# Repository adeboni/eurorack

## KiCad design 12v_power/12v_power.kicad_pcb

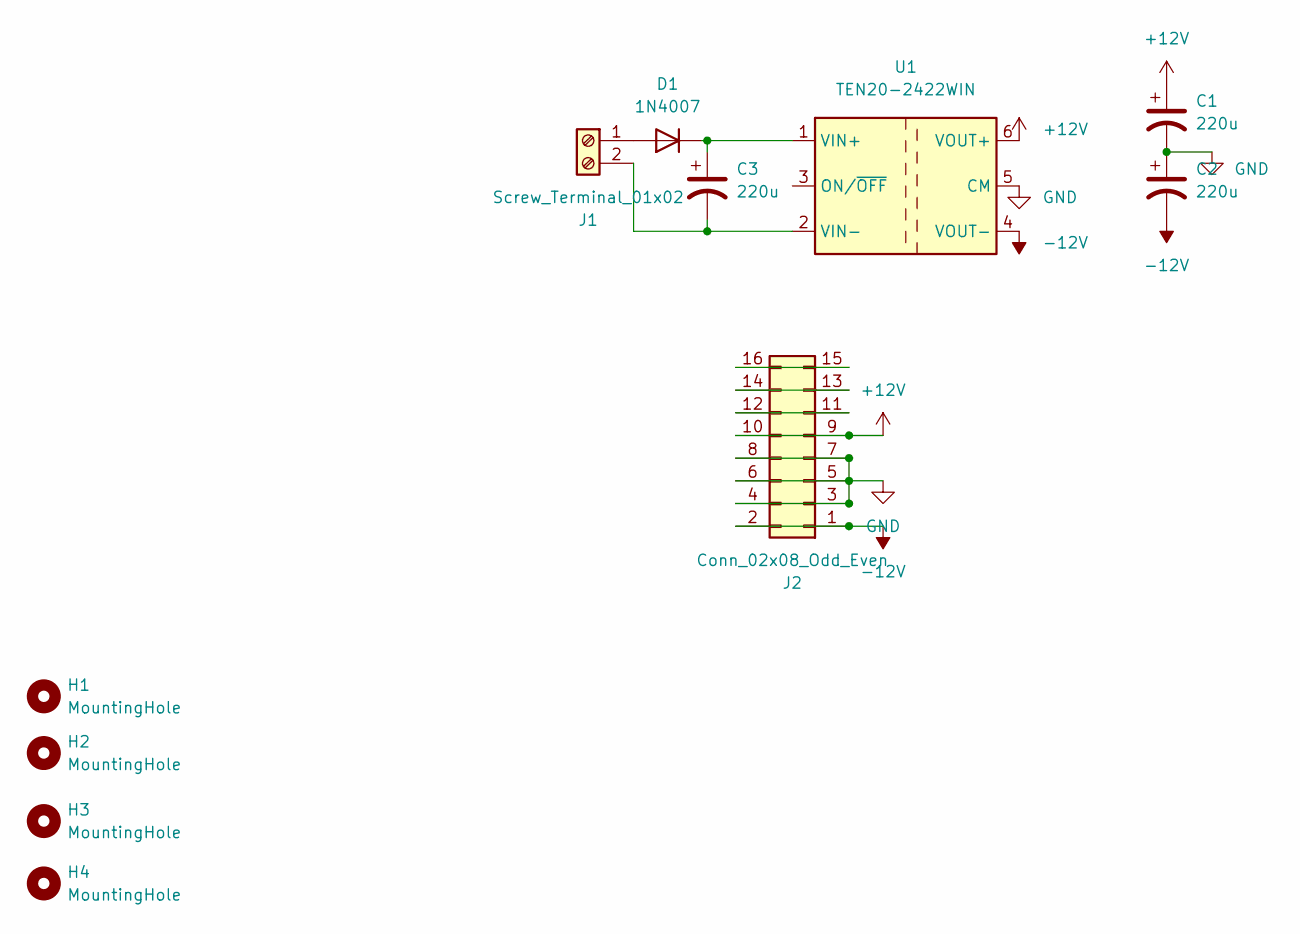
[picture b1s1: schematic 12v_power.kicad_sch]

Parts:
C1, C2, C3: 220u; CP_Radial_D10.0mm_P5.00mm
D1: 1N4007; D_DO-41_SOD81_P10.16mm_Horizontal
H1, H2, H3, H4: MountingHole; MountingHole_3.2mm_M3
J1: Screw_Terminal_01x02; TerminalBlock_Phoenix_MKDS-3-2-5.08_1x02_P5.08mm_Horizontal
J2: Conn_02x08_Odd_Even; IDC-Header_2x08_P2.54mm_Vertical
U1: TEN20-2422WIN; CONV_PYBE30-Q24-D12

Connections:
+12V: C1.1, J2.9, J2.10, U1.6 (VOUT+)
-12V: C2.2, J2.1, J2.2, U1.4 (VOUT-)
GND: C1.2, C2.1, J2.3, J2.4, J2.5, J2.6, J2.7, J2.8, U1.5 (CM)
unnamed: C3.1, D1.1 (K), U1.1 (VIN+)
unnamed: C3.2, J1.2, U1.2 (VIN-)
unnamed: D1.2 (A), J1.1
unnamed: J2.11, J2.12
unnamed: J2.13, J2.14
unnamed: J2.15, J2.16

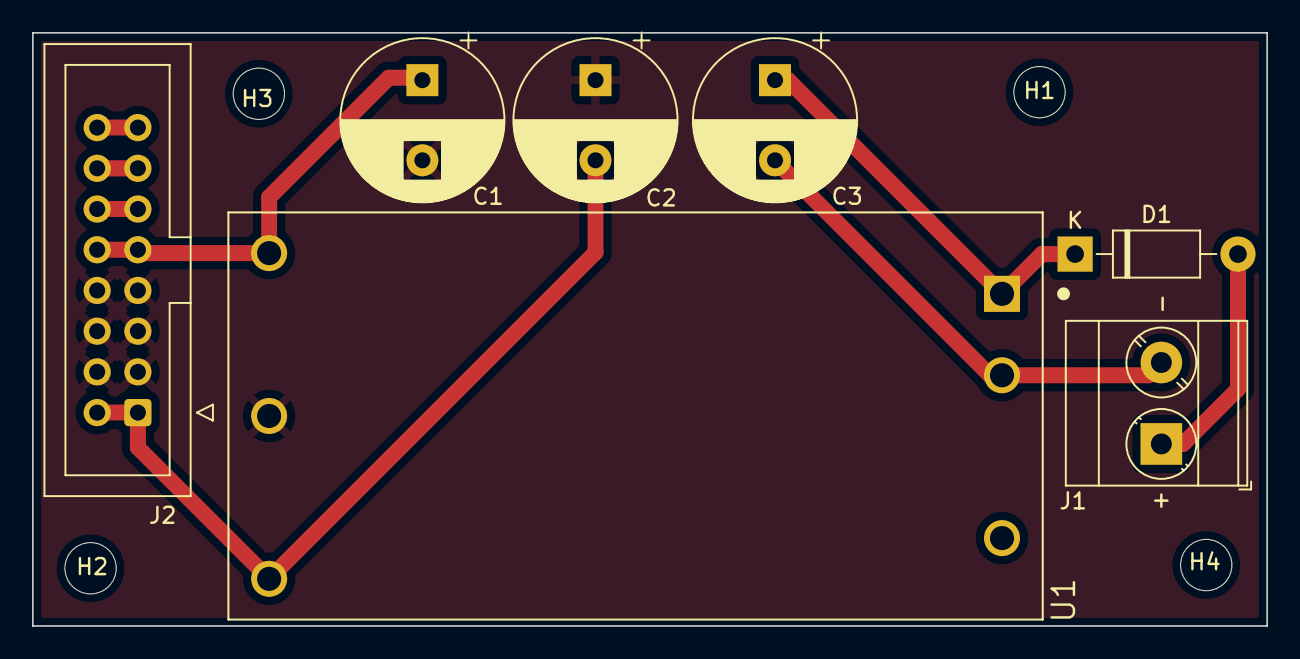
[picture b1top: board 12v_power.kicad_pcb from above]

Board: 2 copper layers, 77.0 x 37.0 mm, 11 parts (0 on the bottom side), 9 nets.

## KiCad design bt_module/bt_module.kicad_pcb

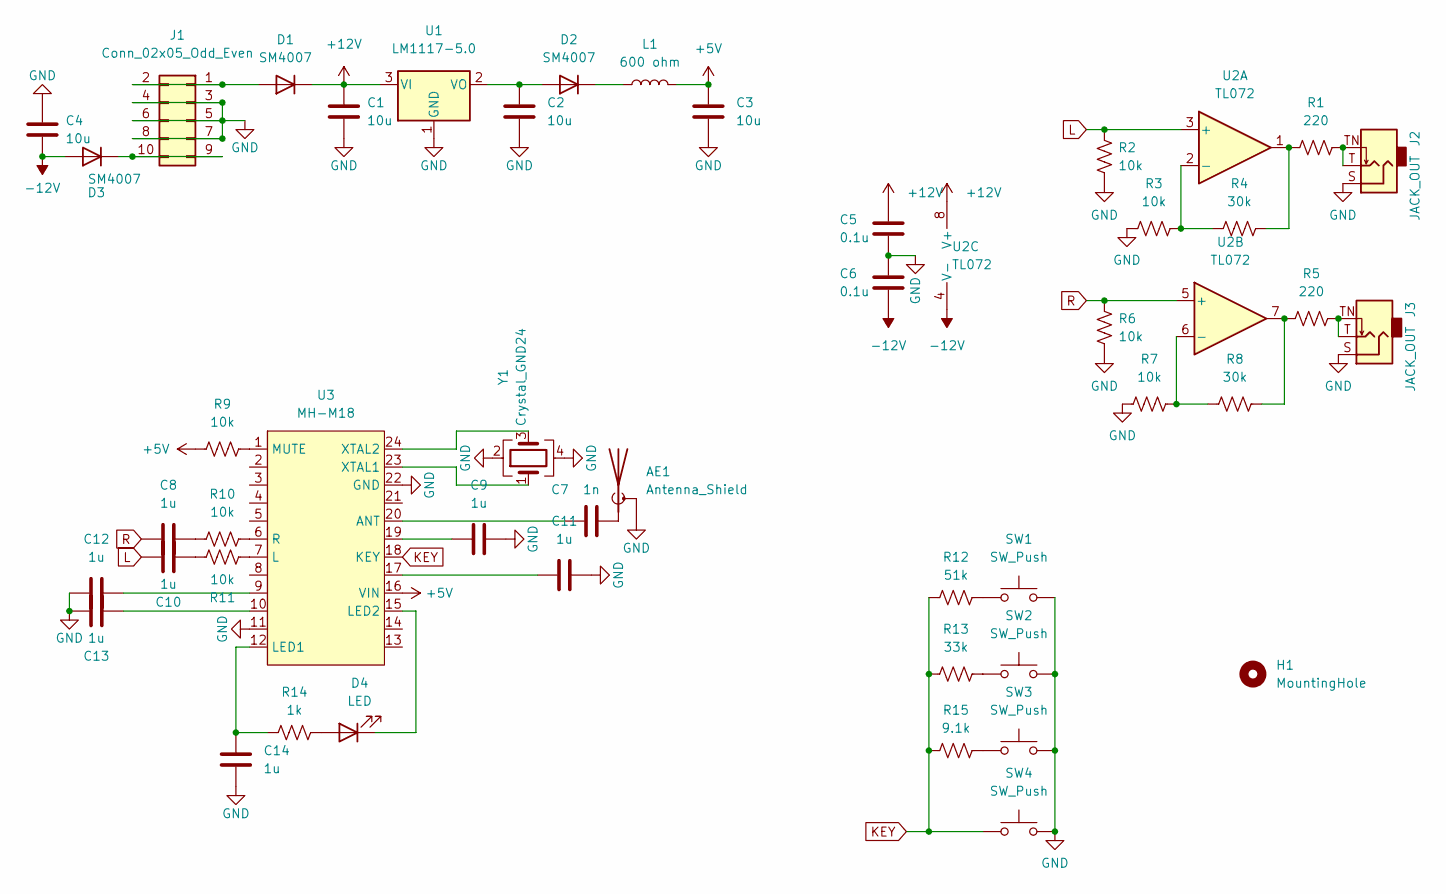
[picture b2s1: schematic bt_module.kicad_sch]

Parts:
AE1: Antenna_Shield; Texas_SWRA117D_2.4GHz_Right
C1, C2, C3, C4: 10u; C_0603_1608Metric
C5, C6: 0.1u; C_0603_1608Metric
C7: 1n; C_0603_1608Metric
C8, C9, C10, C11, C12, C13, C14: 1u; C_0603_1608Metric
D1, D2, D3: SM4007; D_SOD-123
D4: LED; LED_D3.0mm
H1: MountingHole; MountingHole_2.2mm_M2
J1: Conn_02x05_Odd_Even; Pins_2x05_2.54mm_TH_Europower
J2, J3: JACK_OUT; Jack_3.5mm_QingPu_WQP-PJ398SM_Vertical_CircularHoles
L1: 600 ohm; L_0603_1608Metric
R1, R5: 220; R_0603_1608Metric
R2, R3, R6, R7, R9, R10, R11: 10k; R_0603_1608Metric
R4, R8: 30k; R_0603_1608Metric
R12: 51k; R_0603_1608Metric
R13: 33k; R_0603_1608Metric
R14: 1k; R_0603_1608Metric
R15: 9.1k; R_0603_1608Metric
SW1, SW2, SW3, SW4: SW_Push; SW_PUSH_6mm
U1: LM1117-5.0; SOT-223-3_TabPin2
U2: TL072; SOIC-8_3.9x4.9mm_P1.27mm
U3: MH-M18; QSOP-24_3.9x8.7mm_P0.635mm
Y1: Crystal_GND24; Crystal_SMD_2520-4Pin_2.5x2.0mm

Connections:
+5V: C3.1, L1.2, R9.1, U3.16 (VIN)
+12V: C1.1, C5.1, D1.1 (K), U1.3 (VI), U2.8 (V+)
-12V: C4.2, C6.2, D3.2 (A), U2.4 (V-)
GND: AE1.2 (Shield), C1.2, C2.2, C3.2, C4.1, C5.2, C6.1, C9.2, C11.2, C12.1, C13.1, C14.1, J1.3, J1.4, J1.5, J1.6, J1.7, J1.8, J2.S, J3.S, R2.1, R3.1, R6.1, R7.1, SW1.2, SW2.2, SW3.2, SW4.2, U1.1 (GND), U3.11, U3.22 (GND), Y1.2, Y1.4
KEY: R12.1, R13.1, R15.1, SW4.1, U3.18 (KEY)
L: C10.1, R2.2, U2.3 (+)
unnamed: AE1.1 (A), C7.2
unnamed: C2.1, D2.2 (A), U1.2 (VO)
unnamed: C7.1, U3.20 (ANT)
unnamed: C8.2, R10.1
unnamed: C9.1, U3.19
unnamed: C10.2, R11.1
unnamed: C11.1, U3.17
unnamed: C12.2, U3.9
unnamed: C13.2, U3.10
unnamed: C14.2, R14.1, U3.12 (LED1)
unnamed: D1.2 (A), J1.1, J1.2
unnamed: D2.1 (K), L1.1
unnamed: D3.1 (K), J1.9, J1.10
unnamed: D4.1 (K), U3.15 (LED2)
unnamed: D4.2 (A), R14.2
unnamed: J2.T, J2.TN, R1.2
unnamed: J3.T, J3.TN, R5.2
unnamed: R1.1, R4.2, U2.1
unnamed: R3.2, R4.1, U2.2 (-)
unnamed: R5.1, R8.2, U2.7
unnamed: R7.2, R8.1, U2.6 (-)
unnamed: R9.2, U3.1 (MUTE)
unnamed: R10.2, U3.6 (R)
unnamed: R11.2, U3.7 (L)
unnamed: R12.2, SW1.1
unnamed: R13.2, SW2.1
unnamed: R15.2, SW3.1
unnamed: U3.23 (XTAL1), Y1.1
unnamed: U3.24 (XTAL2), Y1.3
R: C8.1, R6.2, U2.5 (+)

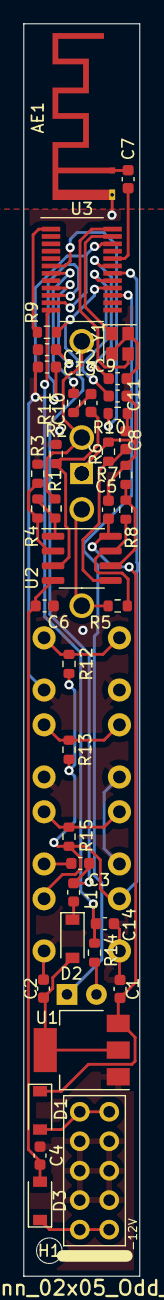
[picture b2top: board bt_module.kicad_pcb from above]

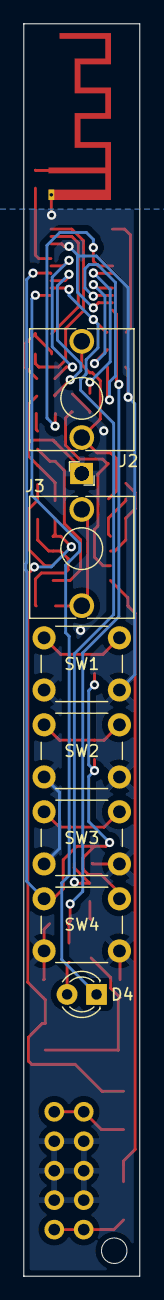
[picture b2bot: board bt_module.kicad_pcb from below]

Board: 2 copper layers, 10.0 x 108.0 mm, 47 parts (7 on the bottom side), 36 nets.

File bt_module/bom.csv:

Comment,Designator,Footprint,LCSC Part Number
9.1k,R15,R_0603_1608Metric,C23260
33k,R13,R_0603_1608Metric,C4216
51k,R12,R_0603_1608Metric,C23196
600 ohm,L1,L_0603_1608Metric,C1002
TL072,U2,SOIC-8_3.9x4.9mm_P1.27mm,C6961
30k,"R8,R4",R_0603_1608Metric,C22984
10k,"R7,R6,R3,R2,R11,R10,R9",R_0603_1608Metric,C25804
220,"R5,R1",R_0603_1608Metric,C22962
SM4007,"D3,D2,D1",D_SOD-123,C64898
0.1u,"C6,C5",C_0603_1608Metric,C14663
10u,"C4,C3,C2,C1",C_0603_1608Metric,C96446
Crystal_GND24,Y1,Crystal_SMD_2520-4Pin_2.5x2.0mm,C284163
LM1117-5.0,U1,SOT-223-3_TabPin2,C6187
1k,R14,R_0603_1608Metric,C21190
1u,"C14,C13,C12,C11,C10,C9,C8",C_0603_1608Metric,C15849
1n,C7,C_0603_1608Metric,C1588

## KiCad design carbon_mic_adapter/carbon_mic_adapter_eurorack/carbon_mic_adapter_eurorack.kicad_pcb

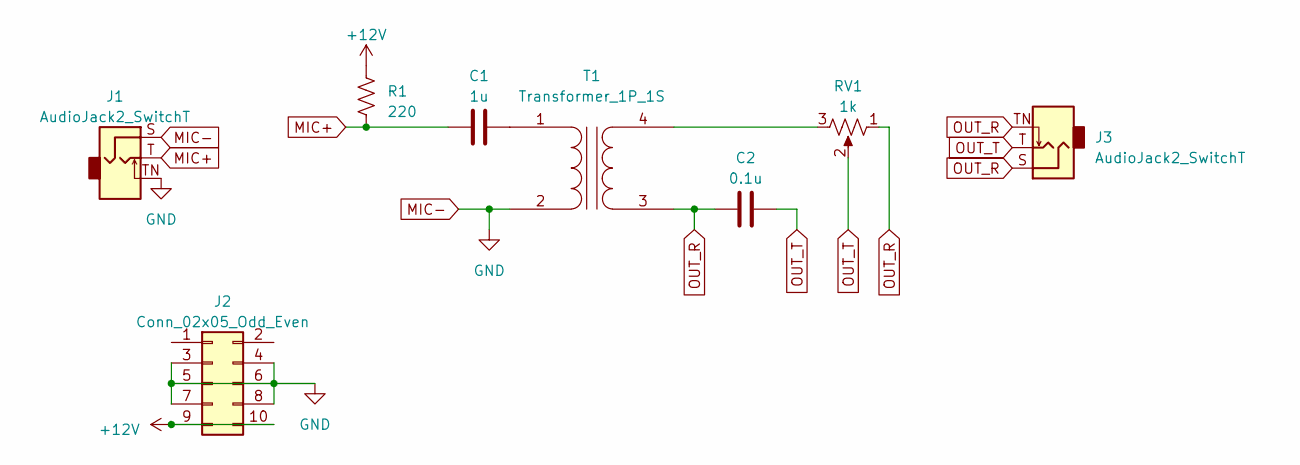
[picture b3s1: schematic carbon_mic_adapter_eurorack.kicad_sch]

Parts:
C1: 1u; C_Disc_P5.08mm
C2: 0.1u; C_Disc_P5.08mm
J1, J3: AudioJack2_SwitchT; Jack_3.5mm_QingPu_WQP-PJ398SM_Vertical_CircularHoles
J2: Conn_02x05_Odd_Even; IDC-Header_2x05_P2.54mm_Vertical
R1: 220; R_Axial_DIN0207_L6.3mm_D2.5mm_P7.62mm_Horizontal
RV1: 1k; Potentiometer_Alpha_RD901F-40-00D_Single_Vertical
T1: Transformer_1P_1S; EI14

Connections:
+12V: J2.9, J2.10, R1.2
MIC+: C1.2, J1.T, R1.1
MIC-: J1.S, J1.TN, J2.3, J2.4, J2.5, J2.6, J2.7, J2.8, T1.2 (AB)
unnamed: C1.1, T1.1 (AA)
unnamed: RV1.3, T1.4 (SB)
OUT_R: C2.1, J3.S, J3.TN, RV1.1, T1.3 (SA)
OUT_T: C2.2, J3.T, RV1.2

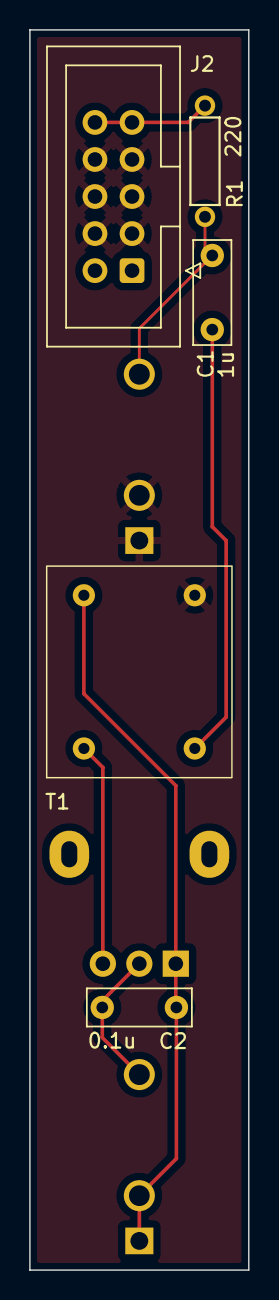
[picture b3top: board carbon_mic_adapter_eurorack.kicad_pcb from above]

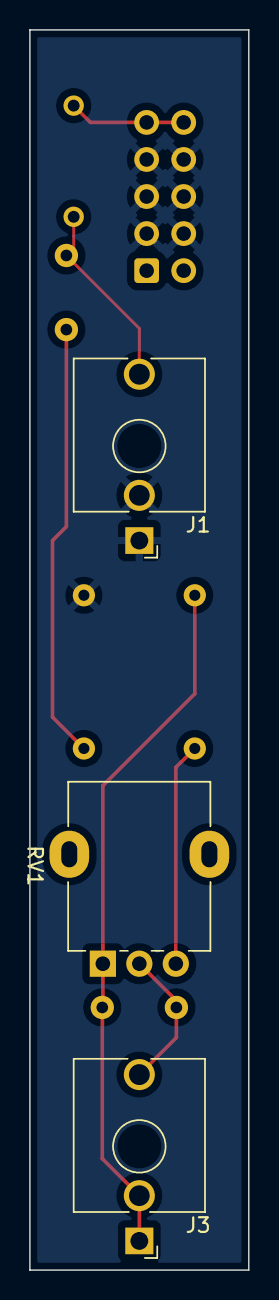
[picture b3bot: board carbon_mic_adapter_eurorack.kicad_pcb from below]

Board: 2 copper layers, 15.0 x 85.0 mm, 8 parts (3 on the bottom side), 7 nets.

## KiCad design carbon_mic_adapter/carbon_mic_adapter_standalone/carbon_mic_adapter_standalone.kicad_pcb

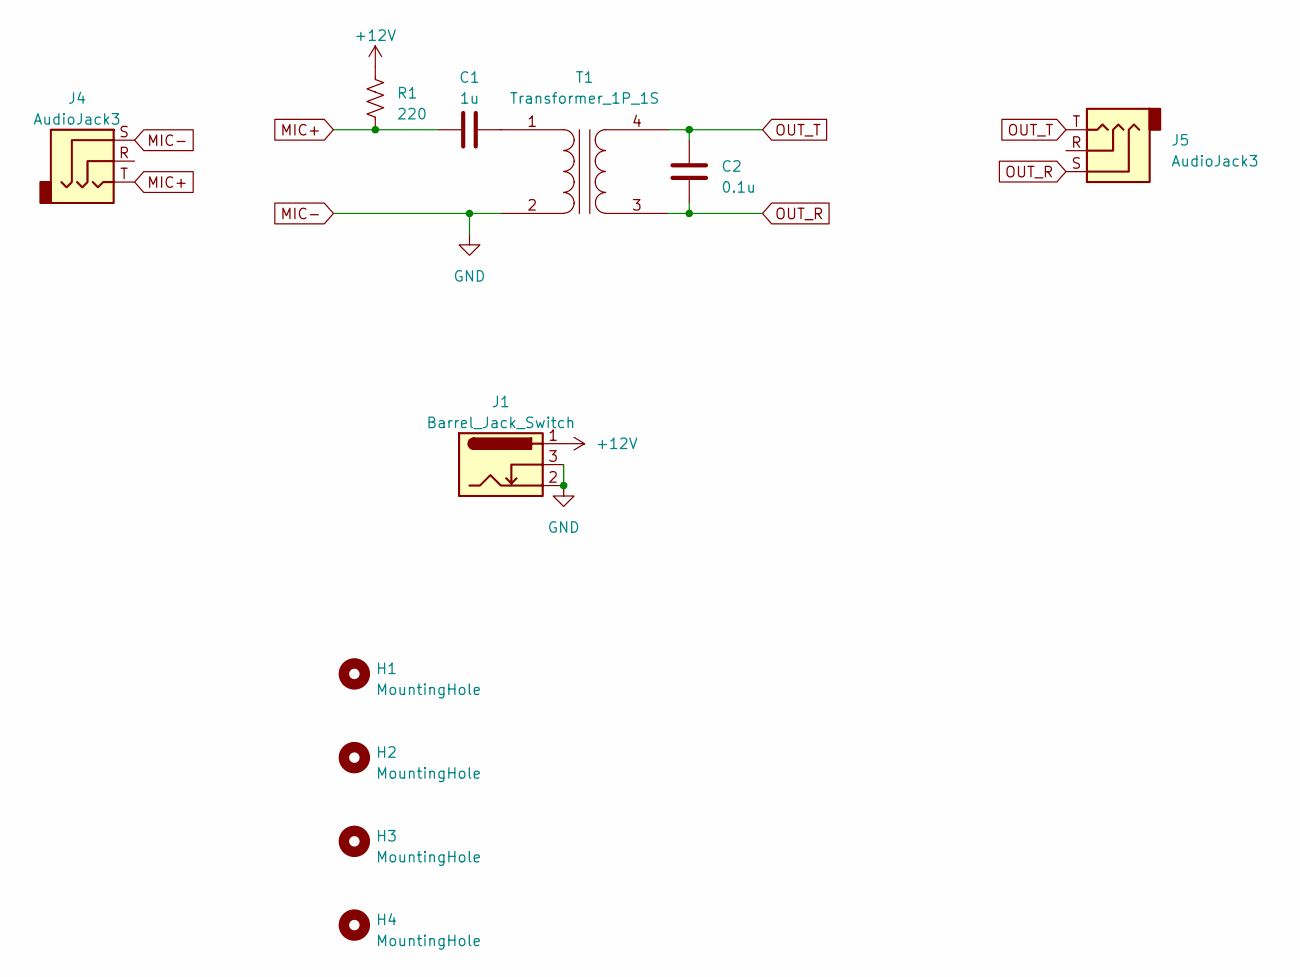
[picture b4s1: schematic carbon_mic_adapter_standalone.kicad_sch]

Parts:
C1: 1u; C_0603_1608Metric
C2: 0.1u; C_0603_1608Metric
H1, H2, H3, H4: MountingHole; MountingHole_3.2mm_M3
J1: Barrel_Jack_Switch; BarrelJack_CLIFF_FC681465S_SMT_Horizontal
J4, J5: AudioJack3; Jack_3.5mm_CUI_SJ-3523-SMT_Horizontal
R1: 220; R_0603_1608Metric
T1: Transformer_1P_1S; EI14

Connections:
+12V: J1.1, R1.2
MIC+: C1.2, J4.T, R1.1
MIC-: J1.2, J1.3, J4.S, T1.2 (AB)
unnamed: C1.1, T1.1 (AA)
OUT_R: C2.1, J5.S, T1.3 (SA)
OUT_T: C2.2, J5.T, T1.4 (SB)

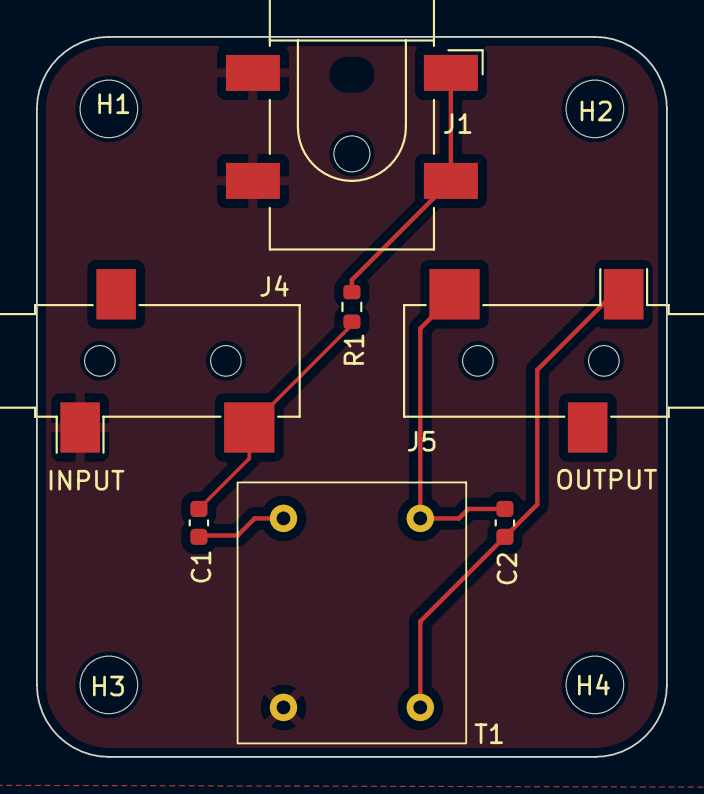
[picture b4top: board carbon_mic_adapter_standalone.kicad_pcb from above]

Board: 2 copper layers, 35.0 x 40.0 mm, 11 parts (0 on the bottom side), 6 nets.

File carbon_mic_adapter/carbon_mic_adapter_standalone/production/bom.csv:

Designator,Footprint,Quantity,Value,LCSC Part #
C1,603,1,1u,C15849
C2,603,1,0.1u,C14663
J1,BarrelJack_CLIFF_FC681465S_SMT_Horizontal,1,Barrel_Jack_Switch,C431534
"J4, J5",Jack_3.5mm_CUI_SJ-3523-SMT_Horizontal,2,AudioJack3,C18594
R1,603,1,220,C22962

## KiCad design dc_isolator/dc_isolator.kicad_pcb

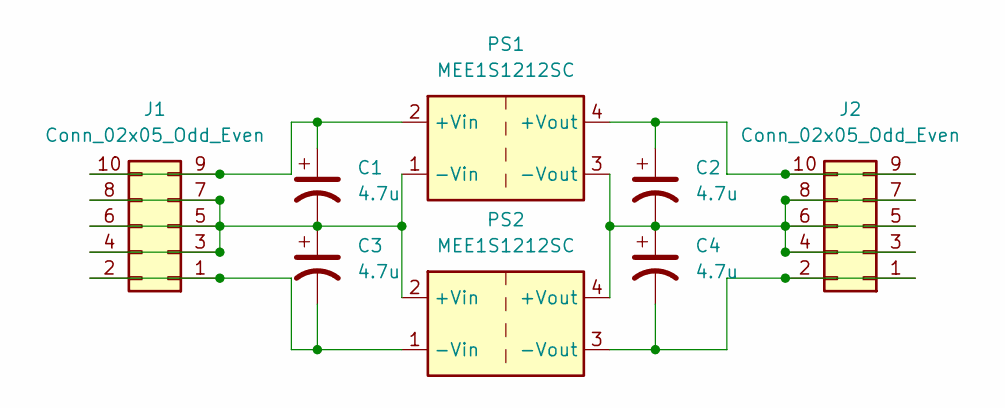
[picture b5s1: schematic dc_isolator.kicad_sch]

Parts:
C1, C2, C3, C4: 4.7u; CP_Radial_D5.0mm_P2.50mm
J1, J2: Conn_02x05_Odd_Even; IDC-Header_2x05_P2.54mm_Vertical
PS1, PS2: MEE1S1212SC; Converter_DCDC_Murata_MEE1SxxxxSC_THT

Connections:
unnamed: C1.1, J1.9, J1.10, PS1.2 (+Vin)
unnamed: C1.2, C3.1, J1.3, J1.4, J1.5, J1.6, J1.7, J1.8, PS1.1 (-Vin), PS2.2 (+Vin)
unnamed: C2.1, J2.9, J2.10, PS1.4 (+Vout)
unnamed: C2.2, C4.1, J2.3, J2.4, J2.5, J2.6, J2.7, J2.8, PS1.3 (-Vout), PS2.4 (+Vout)
unnamed: C3.2, J1.1, J1.2, PS2.1 (-Vin)
unnamed: C4.2, J2.1, J2.2, PS2.3 (-Vout)

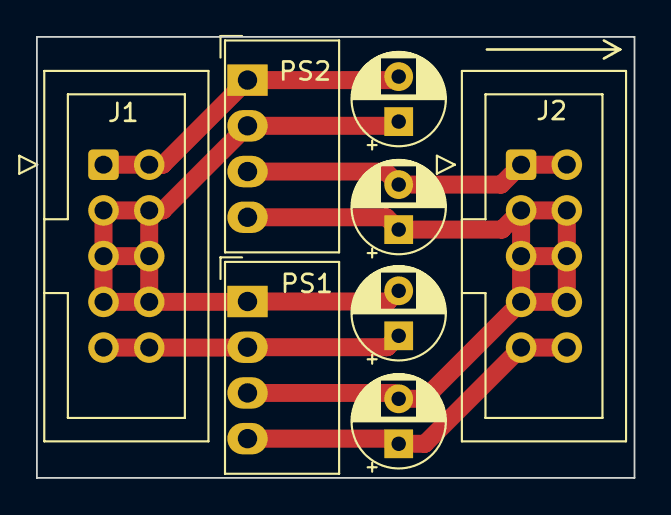
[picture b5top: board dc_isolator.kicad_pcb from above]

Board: 2 copper layers, 33.2 x 24.5 mm, 8 parts (0 on the bottom side), 6 nets.
